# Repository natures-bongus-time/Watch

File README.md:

# Watch:
a watch made on kicad using tft screens and a custom pcb to display images on the screem
made to keep track of what time it is and to count down to important events as  a week four project for hack club half-life.

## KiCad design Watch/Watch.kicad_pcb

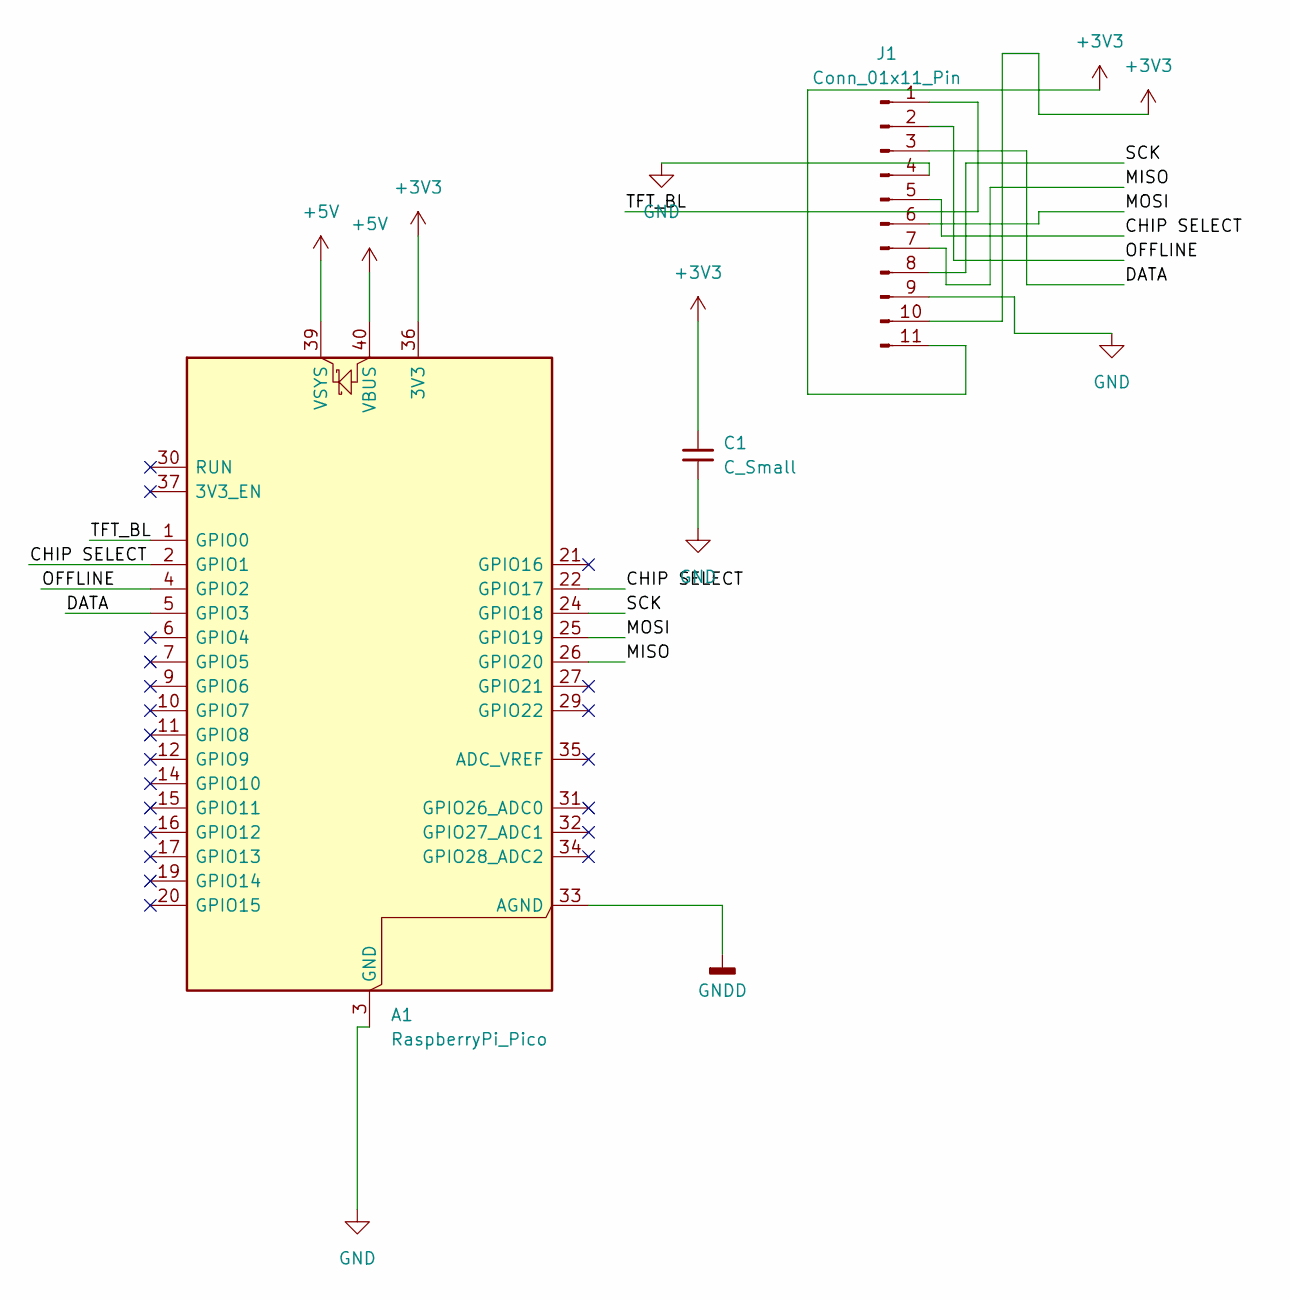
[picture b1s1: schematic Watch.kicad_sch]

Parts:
A1: RaspberryPi_Pico; RaspberryPi_Pico_Common_Unspecified
C1: C_Small; SOIC-8_3.9x4.9mm_P1.27mm
J1: Conn_01x11_Pin; PinHeader_1x11_P2.54mm_Horizontal

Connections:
+3V3: A1.36 (3V3), C1.1, J1.10, J1.11
+5V: A1.39 (VSYS), A1.40 (VBUS)
/CHIP SELECT: A1.2 (GPIO1), A1.22 (GPIO17), J1.5
/DATA: A1.5 (GPIO3), J1.3
/MISO: A1.26 (GPIO20), J1.7
/MOSI: A1.25 (GPIO19), J1.6
/OFFLINE: A1.4 (GPIO2), J1.2
/SCK: A1.24 (GPIO18), J1.8
/TFT_BL: A1.1 (GPIO0), J1.1
GND: A1.3 (GND), A1.8 (GND), A1.13 (GND), A1.18 (GND), A1.23 (GND), A1.28 (GND), A1.38 (GND), C1.2, J1.4, J1.9
GNDD: A1.33 (AGND)

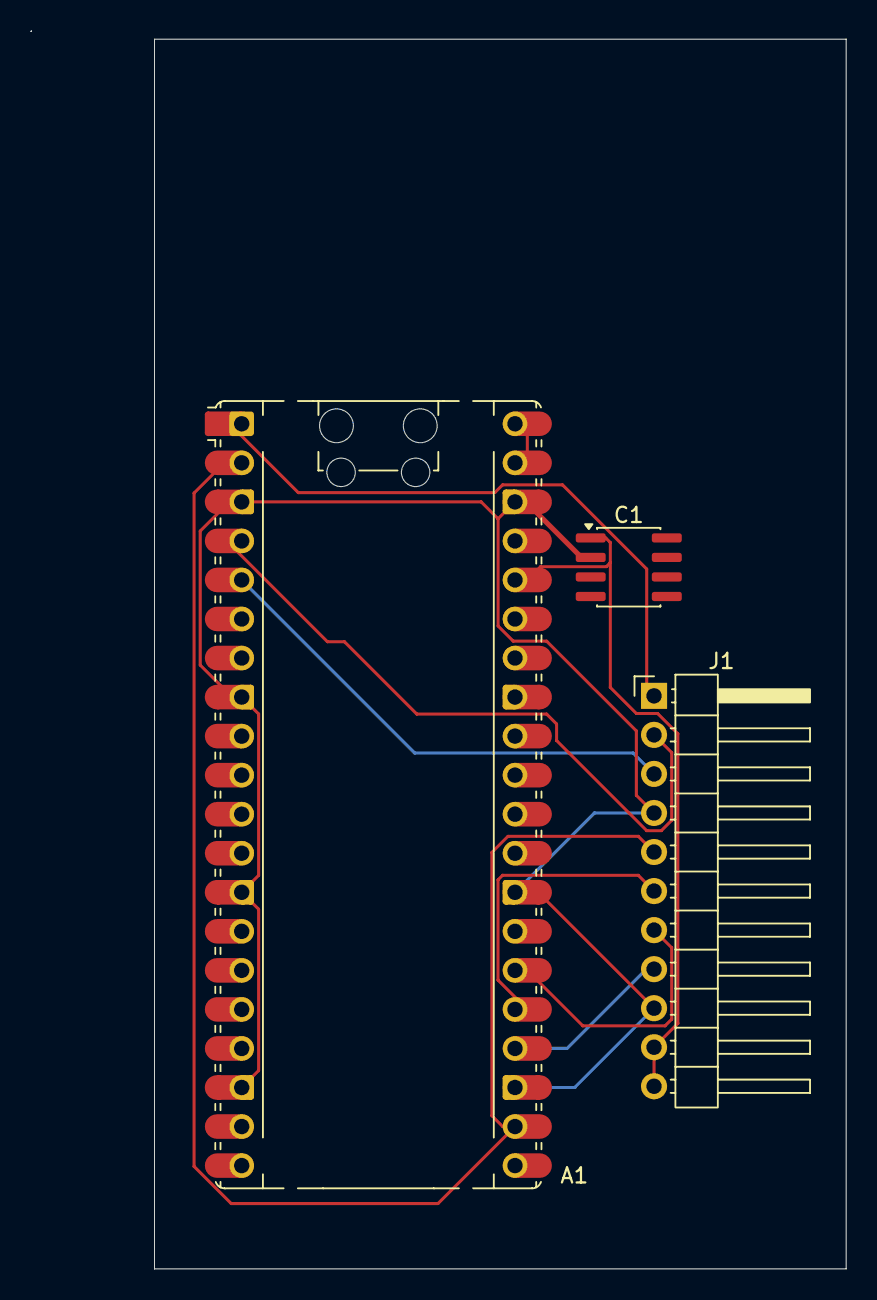
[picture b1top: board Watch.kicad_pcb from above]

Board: 2 copper layers, 45.0 x 80.0 mm, 3 parts (0 on the bottom side), 10 nets.
